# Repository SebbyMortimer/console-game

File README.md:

# Sebby's Console
Welcome to my console project! :)

This was a console, controller, launcher and game made for a Hack Club event that was required to be completed in 4 weeks with one week focussed on each part. It was really fun and challenging (however sometimes stressful near deadlines) and I hope to join in with a few more events in the near future.

My project is centred around the game I created for it, eventually titled "Flynn's Shenanigans", in which the player has to survive natural disasters like meteor showers and tornados on various different maps and um... yeah thats the whole game loop but it's fun though trust. The controller includes buttons that will be mapped to the game including two joysticks for character and camera movement, there's also a couple extra buttons like a button to go back to the launcher or for use in any other games that I make for the console. The launcher was super fun to work on and honestly probably my favourite, it includes three themes from some of my favourite games of all time along with related music for each one. The console I didn't get to spend a lot of time on due to being busy however I got a case design down that will snugly fit a raspberry pi.

## Game

| | | |
| --- | --- | --- |
||||
||||
||||
|||

## Controller

| | |
| --- | --- |
|||

## Launcher

| | |
| --- | --- |
|||

## Console

| | |
| --- | --- |
|||

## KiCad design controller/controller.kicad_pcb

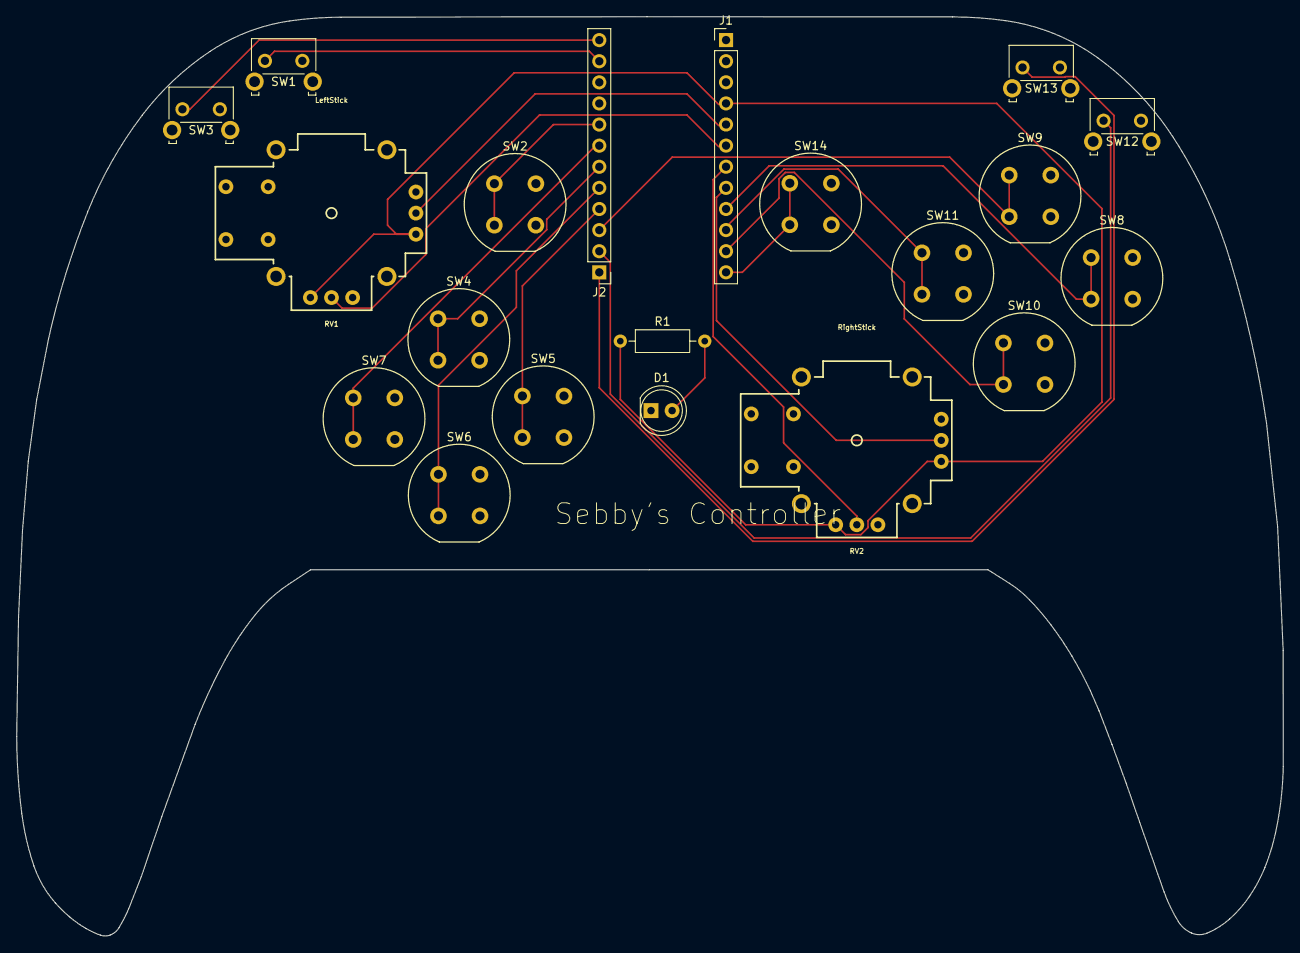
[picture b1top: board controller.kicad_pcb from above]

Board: 2 copper layers, 152.4 x 110.6 mm, 20 parts (0 on the bottom side), 21 nets.

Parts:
D1: LED; LED_D5.0mm
J1, J2: Conn_01x12_Pin; PinHeader_1x12_P2.54mm_Vertical
R1: R; R_Axial_DIN0207_L6.3mm_D2.5mm_P10.16mm_Horizontal
RV1: LeftStick; JOYSTICK
RV2: RightStick; JOYSTICK
SW1: LeftButton; SW_Tactile_SKHH_Angled
SW2: BackButton; Push_E-Switch_KS01Q01
SW3: LeftTrigger; SW_Tactile_SKHH_Angled
SW4: Up; Push_E-Switch_KS01Q01
SW5: Right; Push_E-Switch_KS01Q01
SW6: Down; Push_E-Switch_KS01Q01
SW7: Left; Push_E-Switch_KS01Q01
SW8: B; Push_E-Switch_KS01Q01
SW9: Y; Push_E-Switch_KS01Q01
SW10: A; Push_E-Switch_KS01Q01
SW11: X; Push_E-Switch_KS01Q01
SW12: RightTrigger; SW_Tactile_SKHH_Angled
SW13: RightButton; SW_Tactile_SKHH_Angled
SW14: MenuButton; Push_E-Switch_KS01Q01

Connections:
/A0: J1.8, RV2.5
/A1: J1.7, RV2.2
/A2: J1.6, RV1.2
/A3: J1.5, RV1.5
/D0: J2.12, SW3.1
/D1: J2.11, SW1.1
/D2: J2.8, SW2.1, SW2.3
/D3: J2.7, SW7.1, SW7.3
/D4: J2.6, SW4.1, SW4.3
/D5: J2.5, SW6.1, SW6.3
/D6: J2.4, SW5.1, SW5.3
/D7: J2.3, SW9.1, SW9.3
/D8: J2.2, SW12.1
/D9: J2.1, SW13.1
/D10: J1.12, SW14.1, SW14.3
/D14: J1.10, SW11.1, SW11.3
/D15: J1.9, SW8.1, SW8.3
/D16: J1.11, SW10.1, SW10.3
/GND: D1.1 (K), J1.2, J2.9, J2.10, RV1.3, RV1.6, RV2.3, RV2.6, SW1.2, SW2.2, SW2.4, SW3.2, SW4.2, SW4.4, SW5.2, SW5.4, SW6.2, SW6.4, SW7.2, SW7.4, SW8.2, SW8.4, SW9.2, SW9.4, SW10.2, SW10.4, SW11.2, SW11.4, SW12.2, SW13.2, SW14.2, SW14.4
/VCC: J1.4, R1.1, RV1.1, RV1.4, RV2.1, RV2.4
unnamed: D1.2 (A), R1.2

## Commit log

2026-01-02 Day 1 commit with initial game and journal
2026-01-03 Day 2 commit
2026-01-03 Add image to journal
2026-01-03 Day 3 commit
2026-01-03 Add images for day 3
2026-01-04 Day 4 commit
2026-01-04 Add day 4 progress
2026-01-05 Day 5 commit
2026-01-05 Add image for day 5
2026-01-06 Day 6 commit
2026-01-06 Update journal for day 6
2026-01-08 Day 8 commit
2026-01-08 Fix dialog
2026-01-08 Add images for day 8
2026-01-09 Day 9 commit
2026-01-10 Add video for day 9
2026-01-11 Day 10 commit
2026-01-11 Add image for day 10
2026-01-11 Day 11 commit
2026-01-11 Update journal for day 11
2026-01-11 fix meteor error
2026-01-11 fix meteors fr this time
2026-01-15 Add controller files
2026-01-18 New controller design
2026-01-18 Add images for controller day 7 and clean up journal
2026-01-19 Launcher day 1
2026-01-19 Add image for launcher day 1
2026-01-19 Fix formatting
2026-01-21 Launcher day 3 commit
2026-01-21 Add image for launcher day 3
2026-01-26 Update journal for launcher day 7
2026-01-26 Launcher day 7 commit
2026-02-08 Add console files
2026-02-08 Add images for console
2026-04-03 Worked on readme
